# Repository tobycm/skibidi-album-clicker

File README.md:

# skibidi-album-clicker

alllllll iiiiii wanttttt forr christmassssssssssss, is a tiny 3d printed with some pcb to display photos of the year 🤑🤑🤑🤑🤑🤑🤑🤑🤑

this is a perfect gift for your loved ones. featuring a seeed xiao rp2040 with 2mb of flash, a 1.3 inch oled display, you can make them take a trip down memory lane with photos, or torture them idk.

## Bill of Materials

| Description | Quantity | Part # | Unit Price | Extended Price USD |
| --- | --- | --- | --- | --- |
| 20V 5A 52M@4.5V,2.4A 1.31W 1V 1 | 10 | FDN304P | 0.099 | 0.99 |
| IC BATT CNTL LI-ION 1CEL SOT23-5 | 5 | MCP73832T-2ACI/OT | 0.76 | 3.80 |
| 20V 3.77A 750MW 33MR@4.5V,5A 850 | 10 | SI2312A | 0.109 | 1.09 |
| RES 2K OHM 1% 1/16W 0402 | 25 | RMCF0402FT2K00 | 0.0048 | 0.12 |
| RES 100K OHM 1% 1/16W 0402 | 50 | RC0402FR-07100KL | 0.0032 | 0.16 |
| RES 470 OHM 1% 1/16W 0402 | 50 | RC0402FR-07470RL | 0.003 | 0.15 |
| ENCODER INCRE QUAD HORIZN PC PIN | 5 | PEC12R-4217F-S0024 | 1.478 | 7.39 |
| ENCODER INCRE QUAD HORIZN PC PIN | 5 | PEC12R-4220F-S0024 | 1.478 | 7.39 |
| XIAO RP2040 | 1 | 102010428 | 4.68 | 4.68 |
| LED AMBER CLEAR 0603 SMD | 10 | 150060AS75000 | 0.15 | 1.50 |
| 60V 115MA 7.5@10V,500MA 225MW N | 10 | 2N7002 | 0.054 | 0.54 |
| DIODE SCHOTTKY 20V 1A SOD123 | 10 | MBRX120LF-TP | 0.236 | 2.36 |
| CAP CER 4.7UF 10V X5R 0603 | 50 | CL10A475KP8NNNC | 0.006 | 0.30 |
| Digikey | 1 | Shipping | 20 | 20.00 |
| Neopixel | 5 | SK6812MINI-E |  |  |
| PCB | 1 | JLCPCB PCB | 4.7 | 4.70 |
| Aliexpress |  | LCDs | 17 | 17.00 |
| **Total** |  |  |  | **72.17** |

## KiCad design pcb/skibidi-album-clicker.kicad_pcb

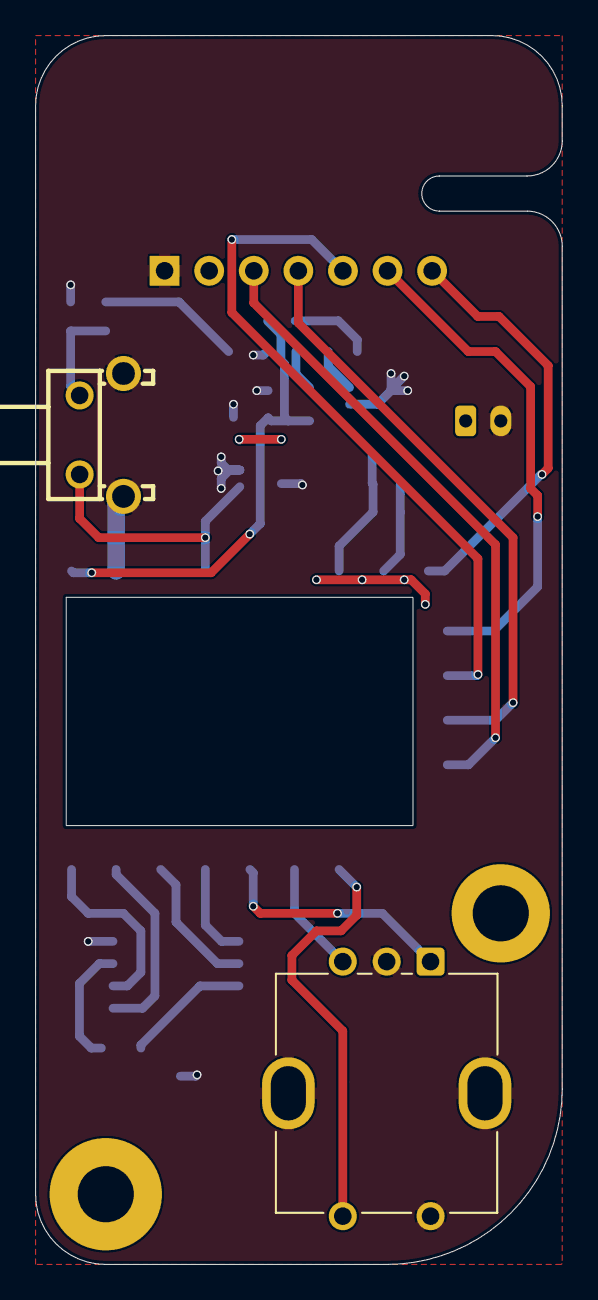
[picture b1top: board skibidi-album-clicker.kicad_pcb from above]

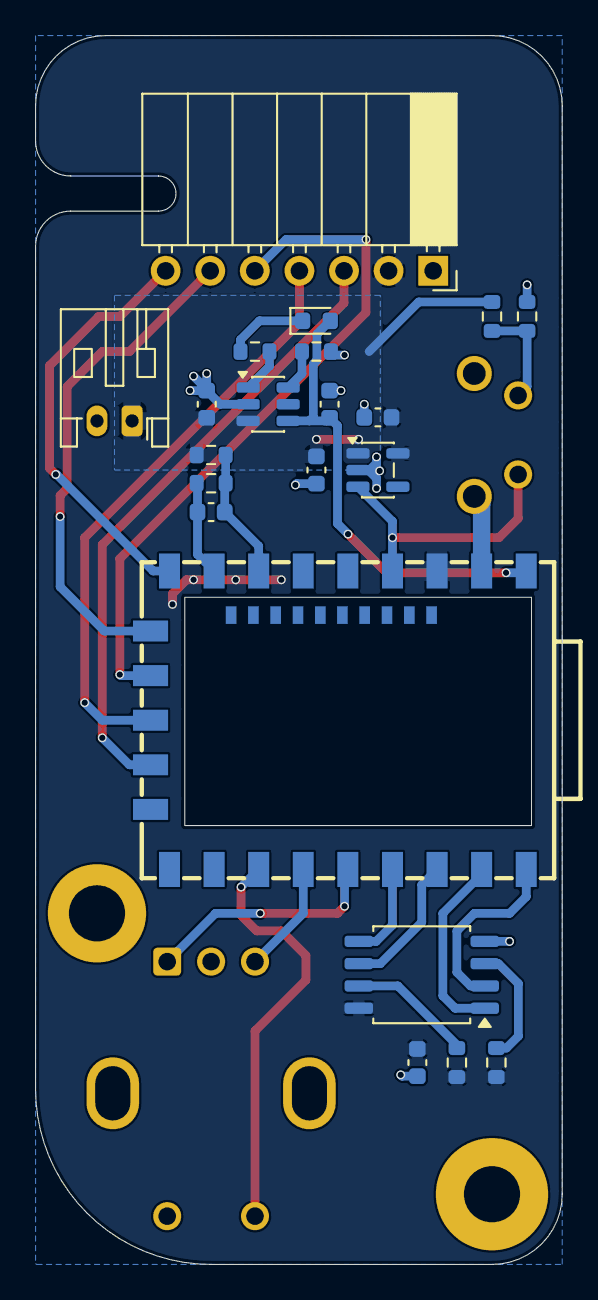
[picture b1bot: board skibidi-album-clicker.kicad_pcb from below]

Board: 2 copper layers, 30.0 x 70.0 mm, 25 parts (21 on the bottom side), 25 nets.

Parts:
C1, C5, C6, C7, C8: 10u; C_0603_1608Metric
C4: 100n; C_0603_1608Metric
D1: LED; LED_0603_1608Metric
DS1: SPI LCD; PinSocket_1x07_P2.54mm_Horizontal
H1, H2: MountingHole; MountingHole_3.2mm_M3_Pad
J1: Conn_01x02_Socket; JST_PH_S2B-PH-K_1x02_P2.00mm_Horizontal
R1, R2, R3, R4, R5, R6, R8: 2.49k; R_0603_1608Metric
R7: 1k; R_0603_1608Metric
SW1: RotaryEncoder_Switch_MP; RotaryEncoder_Bourns_Vertical_PEC12R-3x17F-Sxxxx
SW2: K2-1102AQ-H4CW-01; SW-TH_K2-1102BQ-G4CW-01
U1: PY25Q128HA-SUH-IR; SOIC-8_5.3x5.3mm_P1.27mm
U2: RP2040-ZERO; COMM-SMD_RP2040-ZERO
U3: TP4057; TSOT-23-6
U4: ME6211C33M5; SOT-23-5

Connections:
+3V3: C1.1, C8.1, DS1.2 (VCC), R1.1, R2.1, U1.8 (VCC), U2.21 (3V3), U4.5 (V_{OUT})
+5V: C5.1, D1.2 (A), U2.23 (5V), U3.4 (V_{CC})
+BATT: C6.1, C7.1, J1.1, R3.1, R5.1, U3.3 (BAT), U4.1 (V_{IN})
/A: SW1.A, U2.5 (GP4)
/B: SW1.B, U2.6 (GP5)
/BLK: DS1.7 (BLK), U2.15 (GP14)
/B_VOLT: C4.1, R5.2, R6.1, U2.17 (GP26)
/B_VOLT_REF: C4.2, R6.2, U2.16 (GP15)
/CS: U1.1 (~CS), U2.2 (GP1)
/DC: DS1.6 (DC), U2.14 (GP13)
/E_SW: SW1.S2, U2.7 (GP6)
/LDO_CE: SW2.2, U2.20 (GP29), U4.3 (CE)
/MISO: U1.2 (DO/IO_{1}), U2.1 (GP0)
/MOSI: U1.5 (DI/IO_{0}), U2.4 (GP3)
/MOSI2: DS1.4 (SDA), U2.12 (GP11)
/RES: DS1.5 (RES), U2.13 (GP12)
/SCK: U1.6 (CLK), U2.3 (GP2)
/SCK2: DS1.3 (SCL), U2.11 (GP10)
GND: C1.2, C5.2, C6.2, C7.2, C8.2, DS1.1 (GND), J1.2, R4.2, R8.2, SW1.C, SW1.S1, SW1.SH, SW2.3, SW2.4, U1.4 (GND), U2.22 (GND), U3.2 (GND), U4.2 (V_{SS})
unnamed: D1.1 (K), R7.1
unnamed: R3.2, R4.1, SW2.1
unnamed: R2.2, U1.7 (~HOLD/~RESET/IO_{3})
unnamed: R1.2, U1.3 (~WP/IO_{2})
unnamed: R8.1, U3.6 (PROG)
unnamed: R7.2, U3.1 (~CHRG)

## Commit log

2025-12-06 done!
2025-12-07 move bom and add more render
2025-12-08 add slop firmware
2025-12-08 ai slop
2025-12-15 add schematic
2026-01-18 add gerber and update bom
2026-04-27 finished routing yeahhhh
